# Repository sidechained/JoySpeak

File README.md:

JoySpeak is an open-hardware joystick controlled speaker kit that can be hung and networked using standard RJ-45 network cables to build large-scale impromptu interactive sound installations. Sounds and gestures can be recorded on each JoySpeak that propagate through the network in unexpected ways and as new nodes are added, the character and range of interactions grows and new modes are unlocked

We plan to take this project to this year's Chaos Communication Congress (40c3) and offer kits to build at the Hardware Hacking Area there. The kit itself teaches modern surface mount soldering techniques alongside knowledge of working with audio codecs and wired networking. Once built, Model Citizen's can choose to loan their kit back to us during the congress, to increase the scale of the installation, then claim it back at the end when they need to leave (coat-check style!)

We want to explore and encourage a more communal way of working with open-hardware kits at festival and events, that are not just about buying an 'owning' an object but about building something collectively where each kit and it's builder contribute to the scope and scale of the installation throughout the event.

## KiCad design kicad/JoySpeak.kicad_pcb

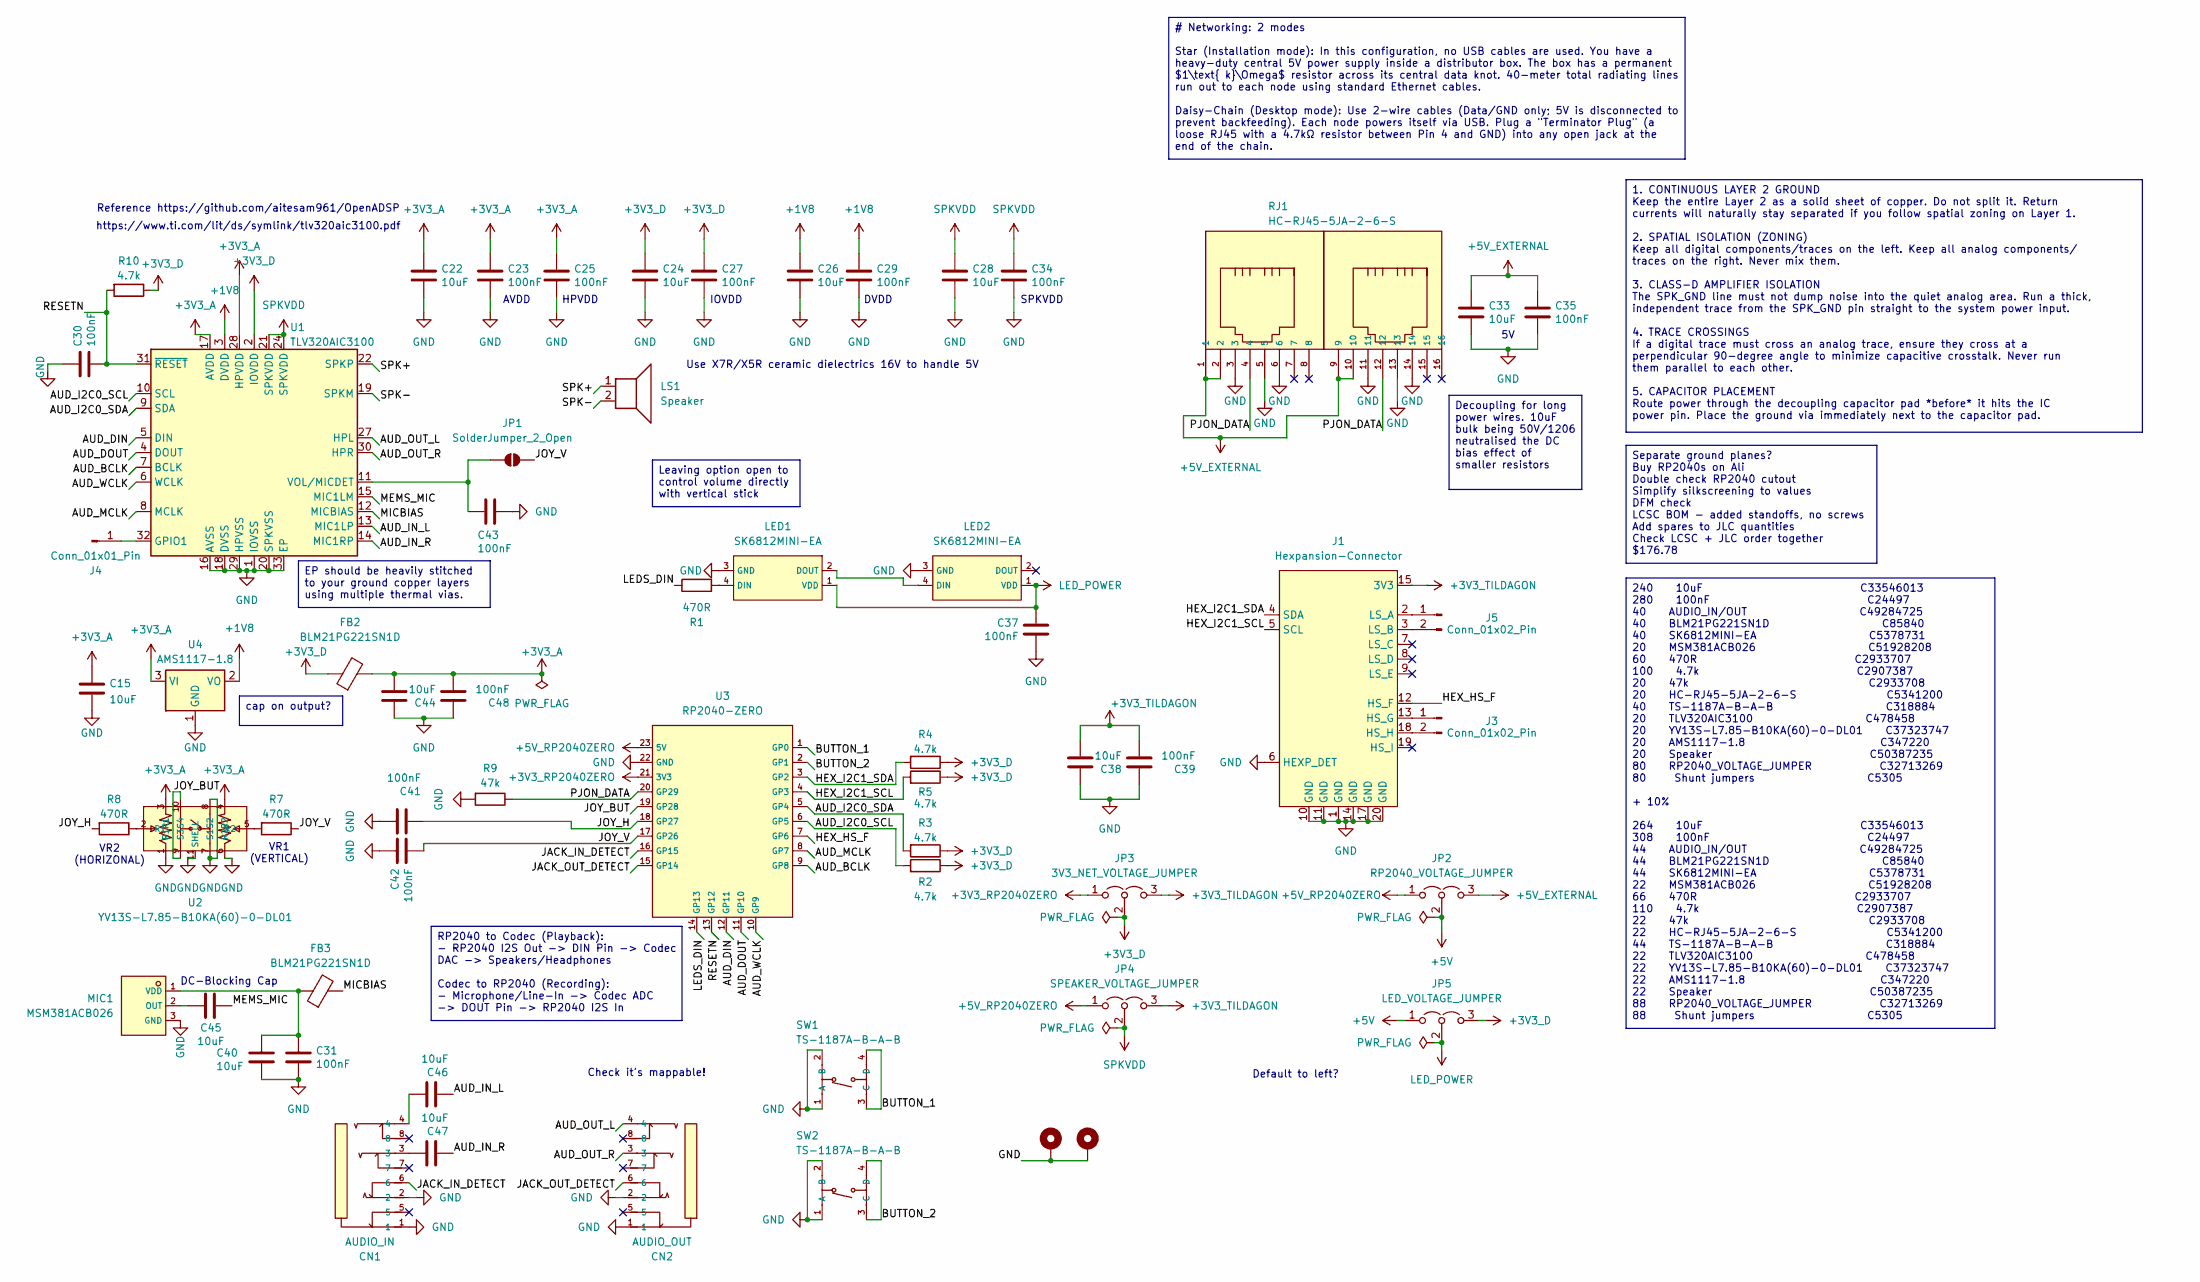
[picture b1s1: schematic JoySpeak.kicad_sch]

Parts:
C15, C22, C24, C26, C28, C33, C38, C40, C44, C45, C46, C47: 10uF; C_1206_3216Metric_Pad1.33x1.80mm_HandSolder; LCSC C33546013
C23, C25, C27, C29, C30, C31, C34, C35, C37, C39, C41, C42, C43, C48: 100nF; C_1206_3216Metric_Pad1.33x1.80mm_HandSolder; LCSC C24497
CN1: AUDIO_IN; C5155561_AUDIO-TH_PJ-393-8P; LCSC C49284725
CN2: AUDIO_OUT; C5155561_AUDIO-TH_PJ-393-8P; LCSC C49284725
FB2, FB3: BLM21PG221SN1D; L_0805_2012Metric_Pad1.05x1.20mm_HandSolder; LCSC C85840
H1, H2: MountingHole_Pad; MountingHole_2.2mm_M2_Pad_Via
J1: Hexpansion-Connector; hexpansion-edge-connector
J3, J5: Conn_01x02_Pin; HexpansionPads1x02
J4: Conn_01x01_Pin; HexpansionPads1x01
JP1: SolderJumper_2_Open; SolderJumper-2_P1.3mm_Open_RoundedPad1.0x1.5mm
JP2: RP2040_VOLTAGE_JUMPER; PinHeader_1x03_P2.54mm_Vertical; LCSC C32713269
JP3: 3V3_NET_VOLTAGE_JUMPER; PinHeader_1x03_P2.54mm_Vertical; LCSC C32713269
JP4: SPEAKER_VOLTAGE_JUMPER; PinHeader_1x03_P2.54mm_Vertical; LCSC C32713269
JP5: LED_VOLTAGE_JUMPER; PinHeader_1x03_P2.54mm_Vertical; LCSC C32713269
LED1, LED2: SK6812MINI-EA; C5378731_LED-SMD_4P-L3_2-W2_8_SK6812MINI-EA; LCSC C5378731
LS1: Speaker; Speaker_XHXDZ-2840-4Ω3W; LCSC C50387235
MIC1: MSM381ACB026; C51928208_MIC-SMD_L2_8-W1_9_MSM381ACB026; LCSC C51928208
R1, R7, R8: 470R; R_1206_3216Metric_Pad1.30x1.75mm_HandSolder; LCSC C2933707
R2, R3, R4, R5, R10: 4.7k; R_1206_3216Metric_Pad1.30x1.75mm_HandSolder; LCSC C2907387
R9: 47k; R_1206_3216Metric_Pad1.30x1.75mm_HandSolder; LCSC C2933708
RJ1: HC-RJ45-5JA-2-6-S; C5341200_RJ45-TH_HC-RJ45-5JA-2-6-S; LCSC C5341200
SW1, SW2: TS-1187A-B-A-B; C318884_SW-SMD_4P-L5_1-W5_1-P3_70-LS6_5-TL_H1_5; LCSC C318884
U1: TLV320AIC3100; VQFN-32-1EP_5x5mm_P0.5mm_EP3.5x3.5mm_ThermalVias; LCSC C478458
U2: YV13S-L7.85-B10KA(60)-0-DL01; C37323747_JOYTICK-TH_YV13S-L7_85-B10KA-60--0-DL01; LCSC C37323747
U3: RP2040-ZERO; C5350143_COMM-SMD_RP2040-ZERO
U4: AMS1117-1.8; SOT-223-3_TabPin2; LCSC C347220

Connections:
+1V8: C26.1, C29.1, U1.3 (DVDD), U4.2 (VO)
+3V3_A: C15.1, C22.1, C23.1, C25.1, C44.1, C48.1, FB2.2, U1.17 (AVDD), U1.28 (HPVDD), U2.3 (R1), U2.4 (R2), U4.3 (VI)
+3V3_D: C24.1, C27.1, FB2.1, JP3.2 (C), JP5.3 (B), R2.1, R3.1, R4.1, R5.1, R10.1, U1.2 (IOVDD)
+3V3_RP2040ZERO: JP3.1 (A), U3.21 (3V3)
+3V3_TILDAGON: C38.1, C39.1, J1.15 (3V3), J1.16 (3V3), JP3.3 (B), JP4.3 (B)
+5V: JP2.2 (C), JP5.1 (A)
+5V_EXTERNAL: C33.1, C35.1, JP2.3 (B), RJ1.1, RJ1.2, RJ1.9, RJ1.10
+5V_RP2040ZERO: JP2.1 (A), JP4.1 (A), U3.23 (5V)
/AUD_BCLK: U1.7 (BCLK), U3.9 (GP8)
/AUD_DIN: U1.5 (DIN), U3.12 (GP11)
/AUD_DOUT: U1.4 (DOUT), U3.11 (GP10)
/AUD_I2C0_SCL: R2.2, U1.10 (SCL), U3.6 (GP5)
/AUD_I2C0_SDA: R3.2, U1.9 (SDA), U3.5 (GP4)
/AUD_IN_L: C46.2, U1.13 (MIC1LP)
/AUD_IN_R: C47.2, U1.14 (MIC1RP)
/AUD_MCLK: U1.8 (MCLK), U3.8 (GP7)
/AUD_OUT_L: CN2.4, U1.27 (HPL)
/AUD_OUT_R: CN2.3, U1.30 (HPR)
/AUD_WCLK: U1.6 (WCLK), U3.10 (GP9)
/BUTTON_1: SW1.3 (C), SW1.4 (D), U3.1 (GP0)
/BUTTON_2: SW2.3 (C), SW2.4 (D), U3.2 (GP1)
/HEX_HS_F: J1.12 (HS_F), U3.7 (GP6)
/HEX_I2C1_SCL: J1.5 (SCL), R5.2, U3.4 (GP3)
/HEX_I2C1_SDA: J1.4 (SDA), R4.2, U3.3 (GP2)
/JACK_IN_DETECT: CN1.6, U3.16 (GP15)
/JACK_OUT_DETECT: CN2.6, U3.15 (GP14)
/JOY_BUT: U2.9 (S3), U2.10 (S4), U3.19 (GP28)
/JOY_H: C41.2, R8.2, U3.18 (GP27)
/JOY_V: C42.2, JP1.2 (B), R7.1, U3.17 (GP26)
/LEDS_DIN: R1.1, U3.14 (GP13)
/MEMS_MIC: C45.1, U1.15 (MIC1LM)
/MICBIAS: FB3.2, U1.12 (MICBIAS)
/PJON_DATA: R9.1, RJ1.4, RJ1.12, U3.20 (GP29)
/RESETN: C30.2, R10.2, U1.31 (~RESET), U3.13 (GP12)
/SPK+: LS1.1 (+), U1.22 (SPKP), U1.26 (SPKP)
/SPK-: LS1.2 (-), U1.19 (SPKM), U1.23 (SPKM)
GND: C15.2, C22.2, C23.2, C24.2, C25.2, C26.2, C27.2, C28.2, C29.2, C30.1, C31.2, C33.2, C34.2, C35.2, C37.2, C38.2, C39.2, C40.2, C41.1, C42.1, C43.1, C44.2, C48.2, CN1.1, CN1.2, CN2.1, CN2.2, H1.1 (1_1), H2.1 (1_1), J1.1 (GND), J1.6 (HEXP_DET), J1.10 (GND), J1.11 (GND), J1.14 (GND), J1.17 (GND), J1.20 (GND), LED1.3 (GND), LED2.3 (GND), MIC1.3 (GND), R9.2, RJ1.3, RJ1.5, RJ1.6, RJ1.11, RJ1.13, RJ1.14, SW1.1 (A), SW1.2 (B), SW2.1 (A), SW2.2 (B), U1.1 (IOVSS), U1.16 (AVSS), U1.18 (DVSS), U1.20 (SPKVSS), U1.25 (SPKVSS), U1.29 (HPVSS), U1.33 (EP), U2.1 (R1), U2.6 (R2), U2.7 (S1), U2.8 (S2), U2.11 (SHELL), U3.22 (GND), U4.1 (GND)
LED_POWER: C37.1, JP5.2 (C), LED1.1 (VDD), LED2.1 (VDD)
unnamed: C46.1, CN1.4
unnamed: C47.1, CN1.3
unnamed: J1.13 (HS_G), J3.1
unnamed: J1.18 (HS_H), J3.2
unnamed: J1.2 (LS_A), J5.1
unnamed: J1.3 (LS_B), J5.2
unnamed: J4.1 (Pin_1_1), U1.32 (GPIO1)
unnamed: C43.2, JP1.1 (A), U1.11 (VOL/MICDET)
unnamed: LED1.4 (DIN), R1.2
unnamed: LED1.2 (DOUT), LED2.4 (DIN)
unnamed: C45.2, MIC1.2 (OUT)
unnamed: C31.1, C40.1, FB3.1, MIC1.1 (VDD)
unnamed: R7.2, U2.5 (R2)
unnamed: R8.1, U2.2 (R1)
SPKVDD: C28.1, C34.1, JP4.2 (C), U1.21 (SPKVDD), U1.24 (SPKVDD)

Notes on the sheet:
Default to left?
IOVDD
HPVDD
Reference https://github.com/aitesam961/OpenADSP
Use X7R/X5R ceramic dielectrics 16V to handle 5V
VR2 (HORIZONAL)
VR1 (VERTICAL)
AVDD
DVDD
https://www.ti.com/lit/ds/symlink/tlv320aic3100.pdf
SPKVDD
Check it's mappable!
DC-Blocking Cap
Decoupling for long power wires. 10uF bulk being 50V/1206 neutralised the DC bias effect of smaller resistors
EP should be heavily stitched to your ground copper layers using multiple thermal vias.
RP2040 to Codec (Playback): - RP2040 I2S Out -> DIN Pin -> Codec DAC -> Speakers/Headphones Codec to RP2040 (Recording): - Microphone/Line-In -> Codec ADC -> DOUT Pin -> RP2040 I2S In
cap on output?
Leaving option open to control volume directly with vertical stick
Separate ground planes? Buy RP2040s on Ali Double check RP2040 cutout Simplify silkscreening to values DFM check LCSC BOM - added standoffs, no screws Add spares to JLC quantities Check LCSC + JLC order together $176.78
# Networking: 2 modes Star (Installation mode): In this configuration, no USB cables are used. You have a heavy-duty central 5V power supply inside a distributor box. The box has a permanent $1\text{ k}\Omega$ resistor across its central data knot. 40-meter total radiating lines run out to each nod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
1. CONTINUOUS LAYER 2 GROUND Keep the entire Layer 2 as a solid sheet of copper. Do not split it. Return currents will naturally stay separated if you follow spatial zoning on Layer 1. 2. SPATIAL ISOLATION (ZONING) Keep all digital components/traces on the left. Keep all analog components/ traces o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
240 10uF C33546013 280 100nF C24497 40 AUDIO_IN/OUT C49284725 40 BLM21PG221SN1D C85840 40 SK6812MINI-EA C5378731 20 MSM381ACB026 C51928208 60 470R C2933707 100 4.7k C2907387 20 47k C2933708 20 HC-RJ45-5JA-2-6-S C5341200 40 TS-1187A-B-A-B C318884 20 TLV320AIC3100 C478458 20 YV13S-L7.85-B10KA(60)-0-D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

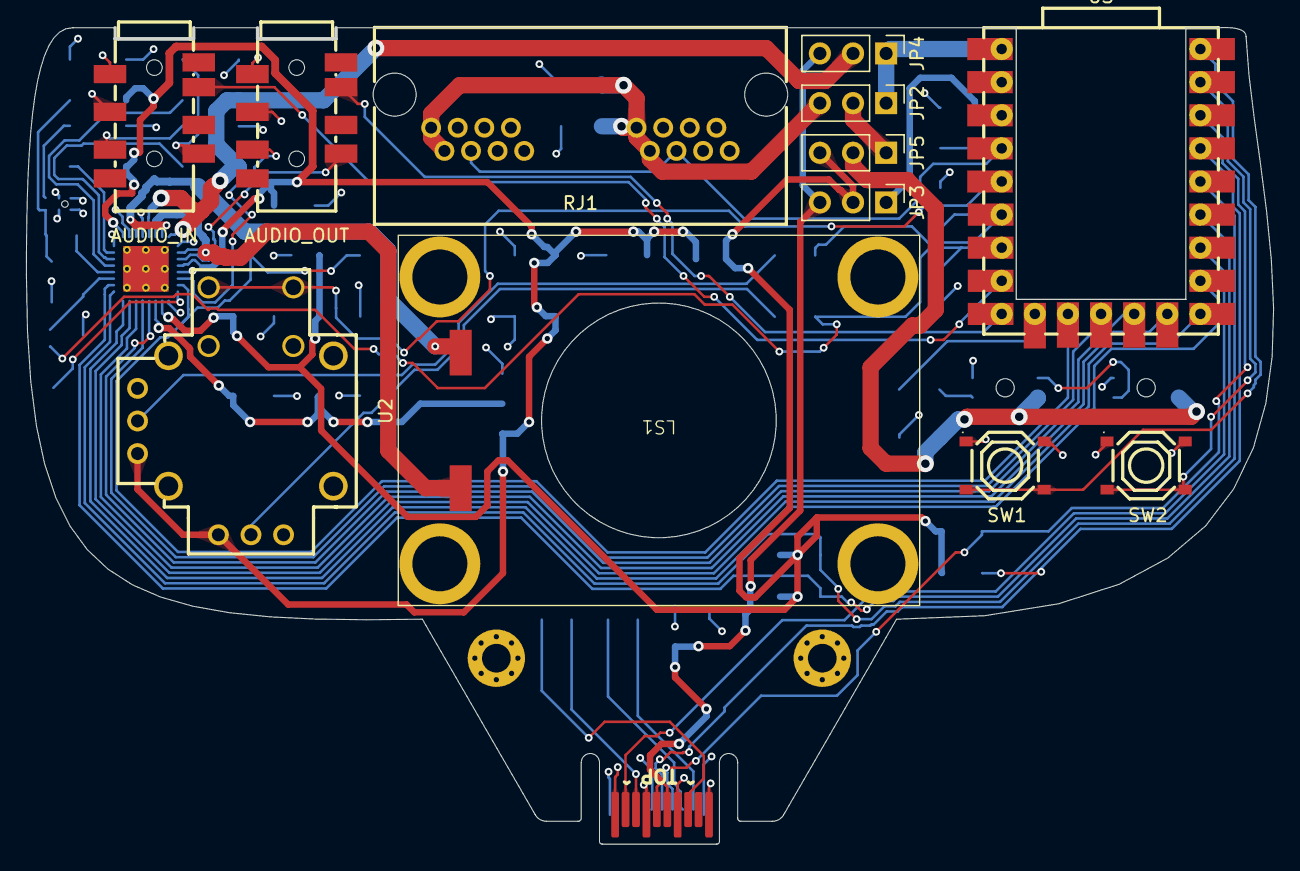
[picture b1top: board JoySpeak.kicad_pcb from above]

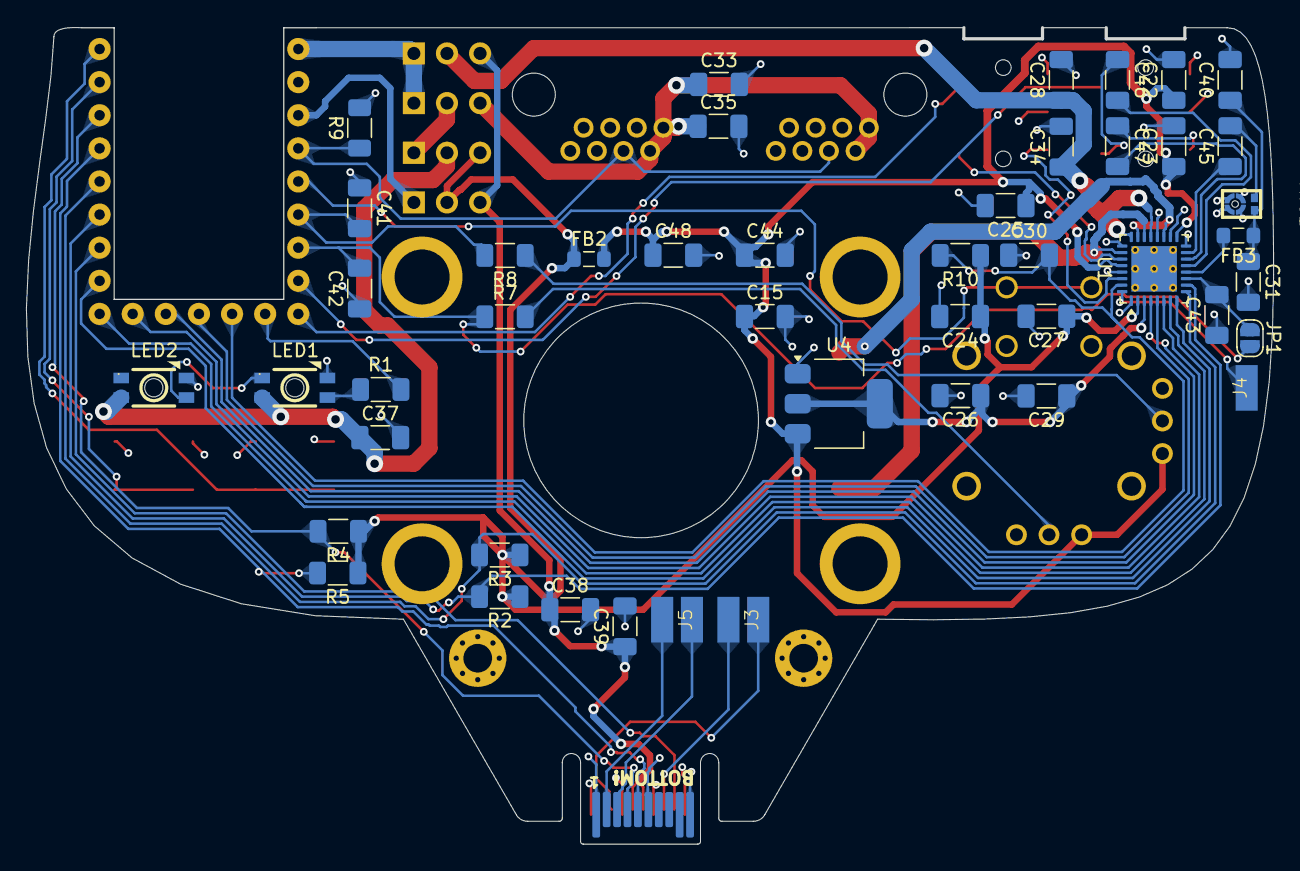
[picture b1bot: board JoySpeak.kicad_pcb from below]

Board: 4 copper layers, 95.7 x 62.6 mm, 61 parts (46 on the bottom side), 53 nets.

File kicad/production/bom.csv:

Designator,Footprint,Quantity,Value,LCSC Part #
"C15, C22, C24, C26, C28, C33, C38, C40, C44, C45, C46, C47",1206,12,10uF,C33546013 
"C23, C25, C27, C29, C30, C31, C34, C35, C37, C39, C41, C42, C43, C48",1206,14,100nF,C24497
CN1,C5155561_AUDIO-TH_PJ-393-8P,1,AUDIO_IN,C5155561 
CN2,C5155561_AUDIO-TH_PJ-393-8P,1,AUDIO_OUT,C5155561
"FB2, FB3",0805,2,BLM21PG221SN1D,C85840
"J3, J5",HexpansionPads1x02,2,Conn_01x02_Pin,
"LED1, LED2",C5378731_LED-SMD_4P-L3_2-W2_8_SK6812MINI-EA,2,SK6812MINI-EA,C5378731
MIC1,C51928208_MIC-SMD_L2_8-W1_9_MSM381ACB026,1,MSM381ACB026,C51928208
"R1, R7, R8",1206,3,470R,C2933707 
"R10, R2, R3, R4, R5",1206,5,4.7k,C2907387 
R9,1206,1,47k,C2933708 
RJ1,C5341200_RJ45-TH_HC-RJ45-5JA-2-6-S,1,HC-RJ45-5JA-2-6-S,C5341200
"SW1, SW2",C318884_SW-SMD_4P-L5_1-W5_1-P3_70-LS6_5-TL_H1_5,2,TS-1187A-B-A-B,C318884
U1,VQFN-32-1EP_5x5mm_P0.5mm_EP3.5x3.5mm_ThermalVias,1,TLV320AIC3100,C478458
U2,C37323747_JOYTICK-TH_YV13S-L7_85-B10KA-60--0-DL01,1,YV13S-L7.85-B10KA(60)-0-DL01,C37323747
U4,SOT-223-3_TabPin2,1,AMS1117-1.8,C347220

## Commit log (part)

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2026-06-14 Commiting before moving from CAN to PJON
2026-06-19 Commiting before simplification
2026-06-19 Started jumpering power. Consolidated cap and resistor values
2026-06-20 Attempted test routing - saving before making layout changes
2026-06-21 Closing in - commiting before adding teardrops
2026-06-21 Committing before flipping RJ45 connector
2026-06-22 Committing before attempting 4-layer layout
2026-06-23 Fixed all DRC errors
2026-06-23 Finalised, pass DFM and sent for fabrication (JLCPCB)
